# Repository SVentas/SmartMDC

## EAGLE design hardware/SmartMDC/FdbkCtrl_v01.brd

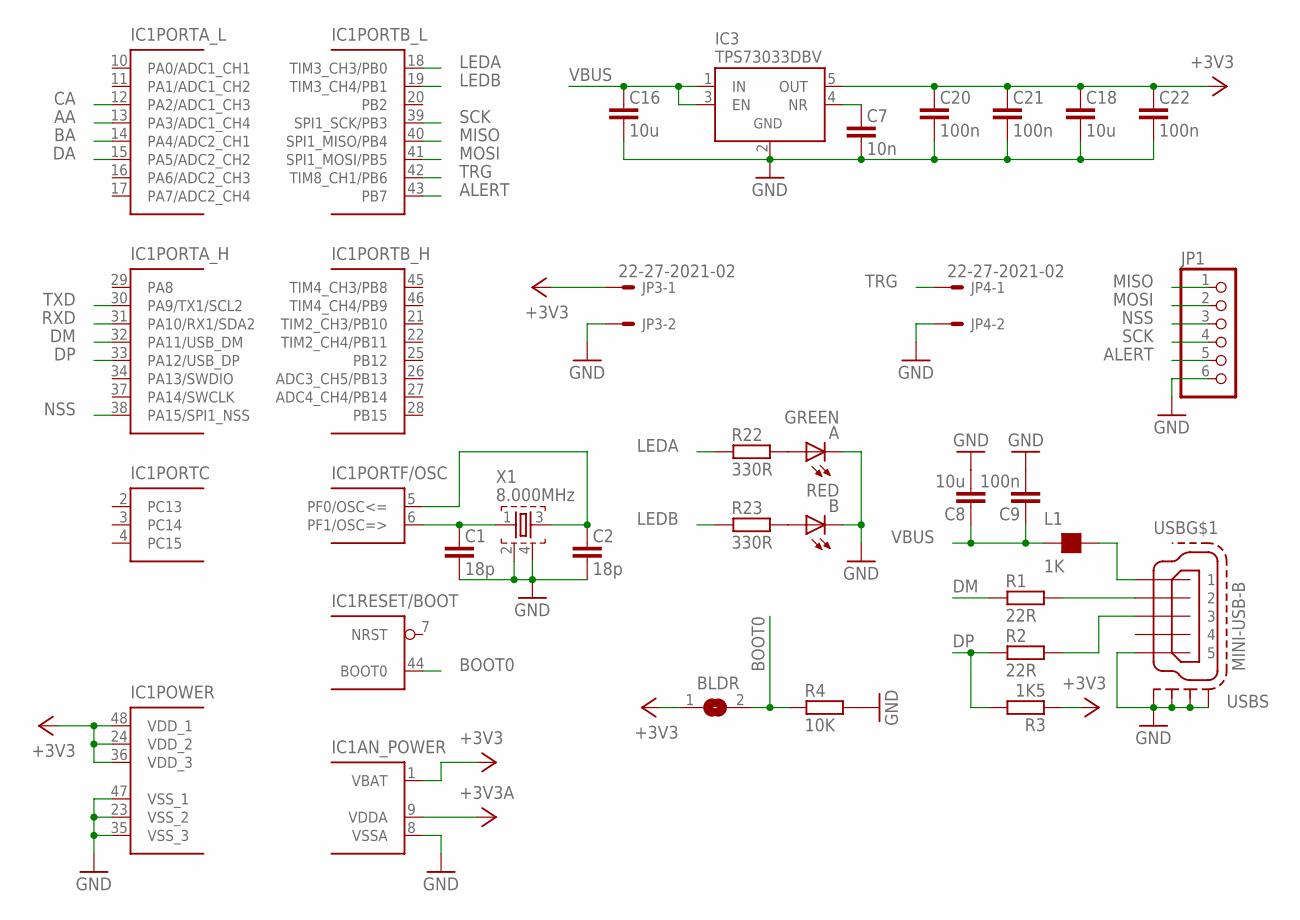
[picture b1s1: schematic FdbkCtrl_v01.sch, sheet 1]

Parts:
A: GREEN; CHIPLED_0805
B: RED; CHIPLED_0805
BLDR: SJ
C1, C2: 18p; C0603G
C7: 10n; C0402G
C8, C16, C18: 10u; C0805G
C9: 100n; C0603G
C20, C21, C22: 100n; C0402G
IC1: STM32F303CXT6; LQFP48
IC3: TPS73033DBV; SOT23-5
JP1: PINHD-1X6; 1X06
JP3, JP4: 22-27-2021-02; 6410-02
L1: 1K; L0603
R1, R2: 22R; R0603
R3: 1K5; R0603
R4: 10K; R0603G
R22, R23: 330R; R0603
USB: MINI-USB-B; 32005-201
X1: 8.000MHz; ABMM2

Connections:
+3V3: BLDR.1, C18.1, C20.1, C21.1, C22.1, IC1.1 (VBAT), IC1.24 (VDD_2), IC1.36 (VDD_3), IC1.48 (VDD_1), IC3.5 (OUT), JP3.1, R3.1
+3V3A: IC1.9 (VDDA); also elsewhere on the board
AA: IC1.13 (PA3/ADC1_CH4); also elsewhere on the board
ALERT: IC1.43 (PB7), JP1.5
BA: IC1.14 (PA4/ADC2_CH1); also elsewhere on the board
BOOT0: BLDR.2, IC1.44 (BOOT0), R4.1
CA: IC1.12 (PA2/ADC1_CH3); also elsewhere on the board
DA: IC1.15 (PA5/ADC2_CH2); also elsewhere on the board
DM: IC1.32 (PA11/USB_DM), R1.1
DP: IC1.33 (PA12/USB_DP), R2.1, R3.2
GND: A.C, B.C, C1.2, C2.2, C7.2, C8.2, C9.2, C16.2, C18.2, C20.2, C21.2, C22.2, IC1.8 (VSSA), IC1.23 (VSS_2), IC1.35 (VSS_3), IC1.47 (VSS_1), IC3.2 (GND), JP1.6, JP3.2, JP4.2, R4.2, USB.5, USB.M1 (S1), USB.M2 (S2), USB.M3 (S3), USB.M4 (S4), X1.2, X1.4; also elsewhere on the board
LEDA: IC1.18 (TIM3_CH3/PB0), R22.1
LEDB: IC1.19 (TIM3_CH4/PB1), R23.1
MISO: IC1.40 (SPI1_MISO/PB4), JP1.1
MOSI: IC1.41 (SPI1_MOSI/PB5), JP1.2
unnamed: C1.1, IC1.6 (PF1/OSC=>), X1.1
unnamed: C2.1, IC1.5 (PF0/OSC<=), X1.3
unnamed: L1.2, USB.1
unnamed: R1.2, USB.2
unnamed: R2.2, USB.3
unnamed: A.A, R22.2
unnamed: C7.1, IC3.4 (NR)
unnamed: B.A, R23.2
NSS: IC1.38 (PA15/SPI1_NSS), JP1.3
RXD: IC1.31 (PA10/RX1/SDA2)
SCK: IC1.39 (SPI1_SCK/PB3), JP1.4
TRG: IC1.42 (TIM8_CH1/PB6), JP4.1
TXD: IC1.30 (PA9/TX1/SCL2)
VBUS: C8.1, C9.1, C16.1, IC3.1 (IN), IC3.3 (EN), L1.1; also elsewhere on the board

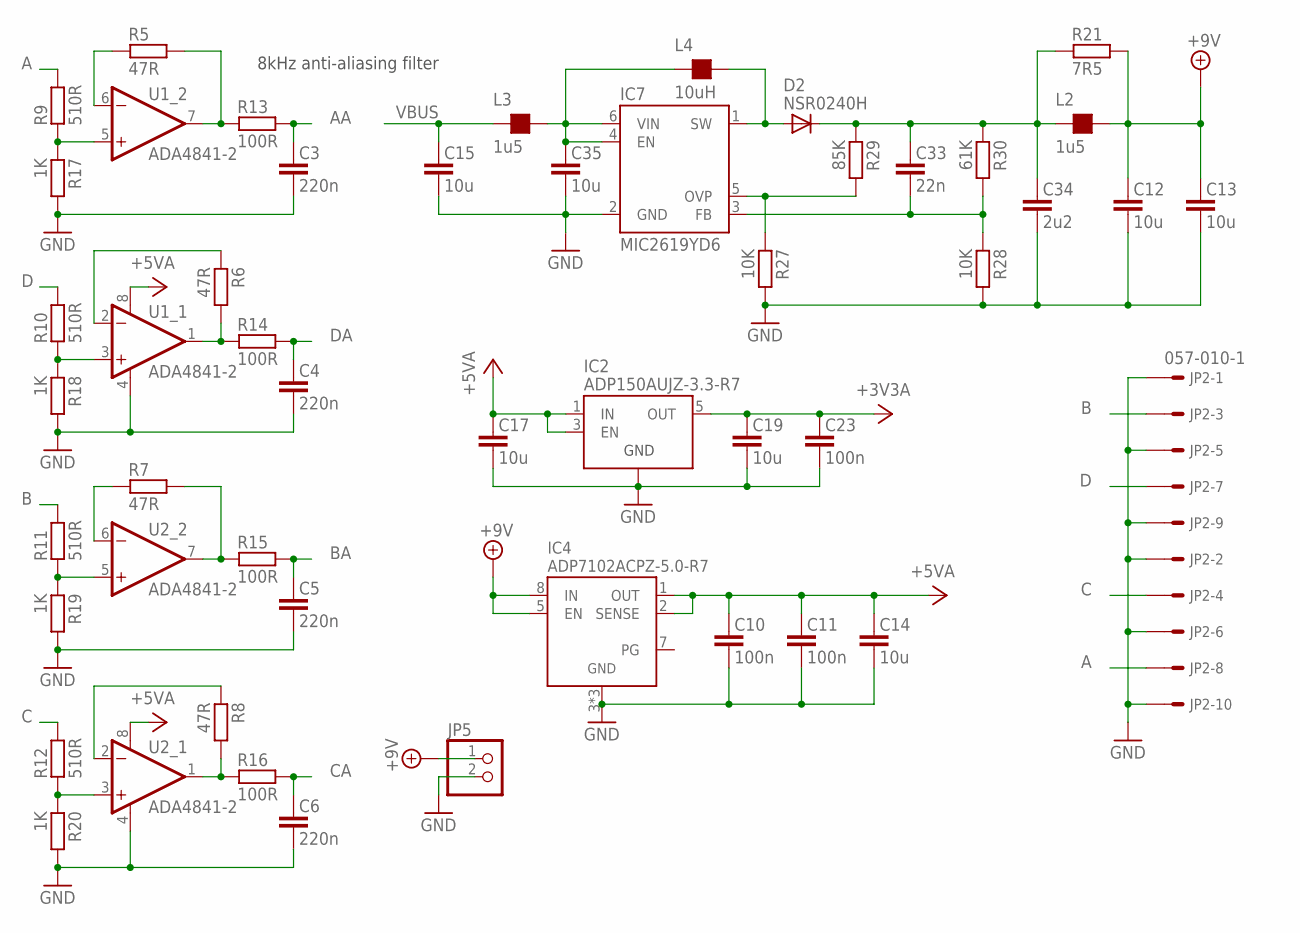
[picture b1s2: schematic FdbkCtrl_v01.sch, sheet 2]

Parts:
C3, C4, C5, C6: 220n; C0603G
C10, C11: 100n; C0603G
C12, C13, C14, C15, C17, C19, C35: 10u; C0805G
C23: 100n; C0402G
C33: 22n; C0603
C34: 2u2; C0805G
D2: NSR0240H; SOD323
IC2: ADP150AUJZ-3.3-R7; SOT23-5
IC4: ADP7102ACPZ-5.0-R7; LFCSP8
IC7: MIC2619YD6; SOT23-6
JP2: 057-010-1
JP5: PINHD-1X2; 1X02
L2, L3: 1u5; L2010
L4: 10uH; L1210
R5, R6, R7, R8: 47R; R0603
R9, R10, R11, R12: 510R; R0603
R13, R14, R15, R16: 100R; R0603
R17, R18, R19, R20: 1K; R0603G
R21: 7R5; R0805
R27, R28: 10K; R0603G
R29: 85K; R0603
R30: 61K; R0603
U1, U2: ADA4841-2; SOIC-8

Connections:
+3V3A: C19.1, C23.1, IC2.5 (OUT); also elsewhere on the board
+5VA: C10.1, C11.1, C14.1, C17.1, IC2.1 (IN), IC2.3 (EN), IC4.1 (OUT), IC4.2 (SENSE), U1.8 (V+), U2.8 (V+)
+9V: C12.1, C13.1, IC4.5 (EN), IC4.8 (IN), JP5.1, L2.2, R21.2
+9VRAW: C33.1, C34.1, D2.C, L2.1, R21.1, R29.1, R30.1
A: JP2.8, R9.2
AA: C3.1, R13.2; also elsewhere on the board
B: JP2.3, R11.2
BA: C5.1, R15.2; also elsewhere on the board
C: JP2.4, R12.2
CA: C6.1, R16.2; also elsewhere on the board
D: JP2.7, R10.2
DA: C4.1, R14.2; also elsewhere on the board
FB: C33.2, IC7.3 (FB), R28.1, R30.2
GND: C3.2, C4.2, C5.2, C6.2, C10.2, C11.2, C12.2, C13.2, C14.2, C15.2, C17.2, C19.2, C23.2, C34.2, C35.2, IC2.2 (GND), IC4.3 (GND), IC4.6 (GND), IC4.EP (GND), IC7.2 (GND), JP2.1, JP2.2, JP2.5, JP2.6, JP2.9, JP2.10, JP5.2, R17.2, R18.2, R19.2, R20.2, R27.2, R28.2, U1.4 (V-), U2.4 (V-); also elsewhere on the board
unnamed: R5.2, R13.1, U1.7 (OUT)
unnamed: R6.2, R14.1, U1.1 (OUT)
unnamed: R7.2, R15.1, U2.7 (OUT)
unnamed: R8.2, R16.1, U2.1 (OUT)
unnamed: R10.1, R18.1, U1.3 (+IN)
unnamed: R11.1, R19.1, U2.5 (+IN)
unnamed: R12.1, R20.1, U2.3 (+IN)
unnamed: R5.1, U1.6 (-IN)
unnamed: R7.1, U2.6 (-IN)
unnamed: R8.1, U2.2 (-IN)
unnamed: R6.1, U1.2 (-IN)
unnamed: R9.1, R17.1, U1.5 (+IN)
OVP: IC7.5 (OVP), R27.1, R29.2
SW: D2.A, IC7.1 (SW), L4.2
VBUS: C15.1, L3.1; also elsewhere on the board
VIN: C35.1, IC7.4 (EN), IC7.6 (VIN), L3.2, L4.1

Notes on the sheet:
8kHz anti-aliasing filter

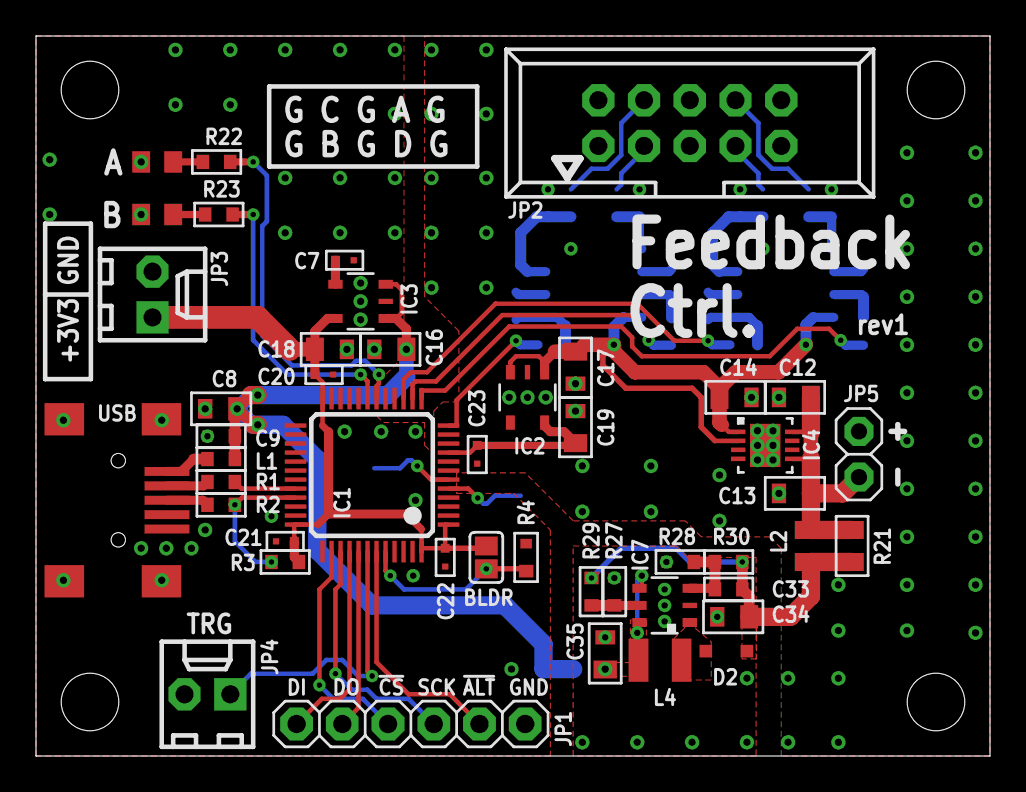
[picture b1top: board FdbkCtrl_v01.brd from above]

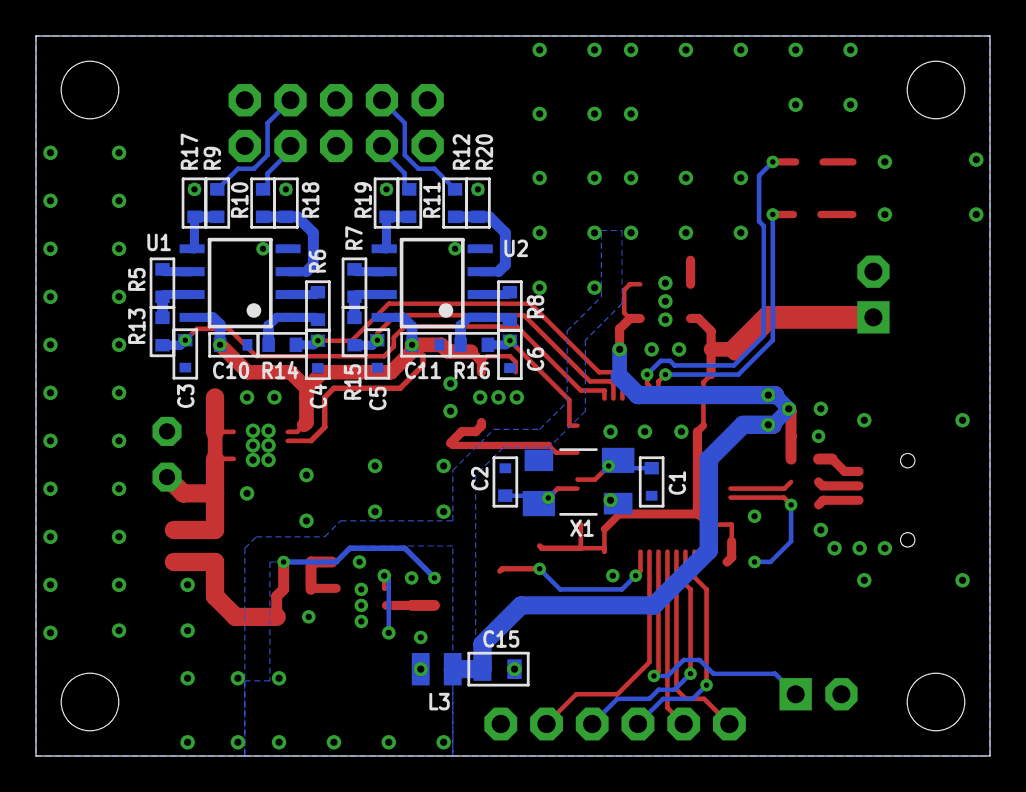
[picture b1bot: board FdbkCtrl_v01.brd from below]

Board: 2 copper layers, 53.0 x 40.0 mm, 75 parts (29 on the bottom side), 50 nets.

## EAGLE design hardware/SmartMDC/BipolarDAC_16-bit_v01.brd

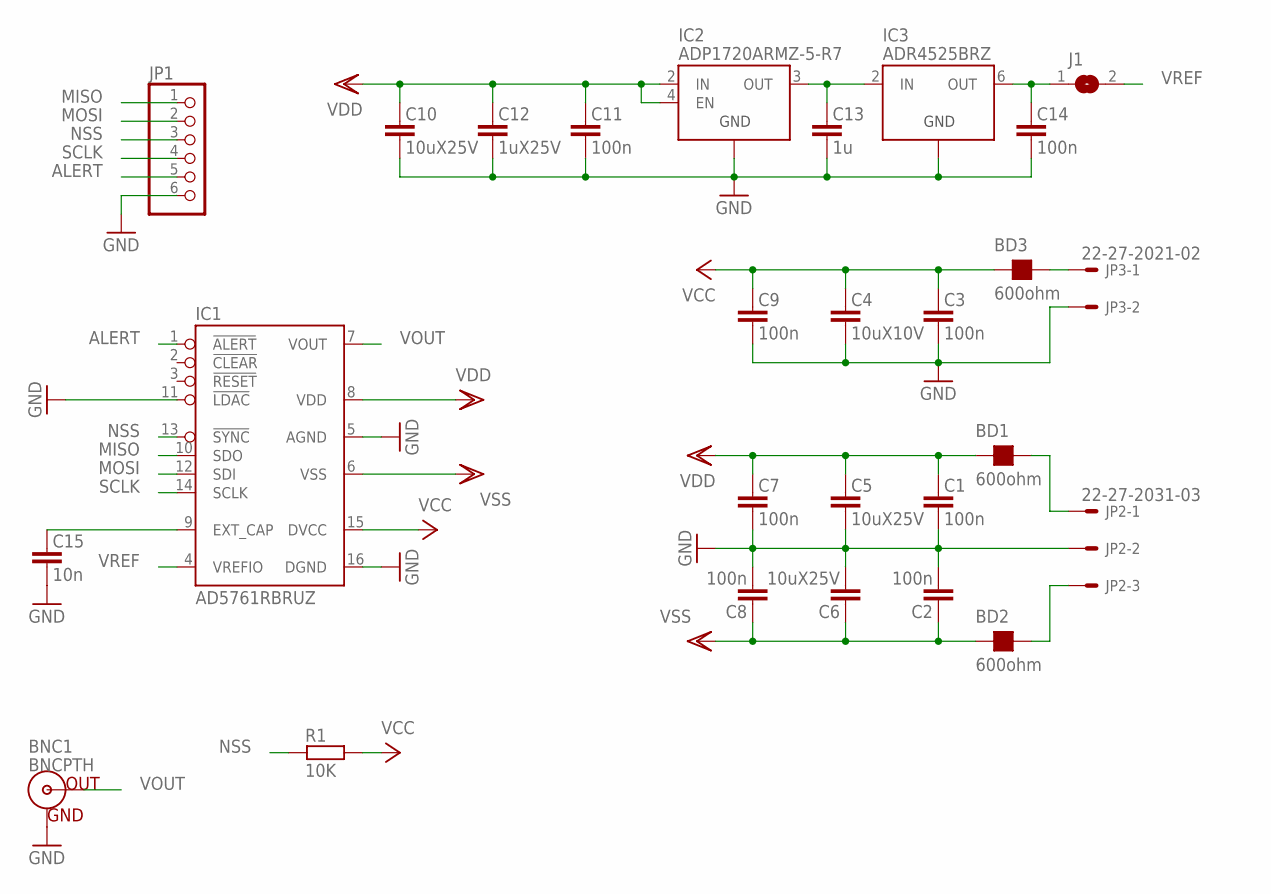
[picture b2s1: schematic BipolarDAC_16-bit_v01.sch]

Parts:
BD1, BD2, BD3: 600ohm; L0805
BNC1: BNCPTH; BNC
C1, C2, C7, C8, C11, C14: 100n; C0603G
C3, C9: 100n; C0402G
C4: 10uX10V; C0805G
C5, C6, C10: 10uX25V; C1206G
C12: 1uX25V; C0603G
C13: 1u; C0603G
C15: 10n; C0603G
IC1: AD5761RBRUZ; TSSOP16
IC2: ADP1720ARMZ-5-R7; MSOP8
IC3: ADR4525BRZ; SOIC-8
J1: SJS
JP1: PINHD-1X6; 1X06
JP2: 22-27-2031-03; 6410-03
JP3: 22-27-2021-02; 6410-02
R1: 10K; R0603G

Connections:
5VOUT: C13.1, IC2.3 (OUT), IC3.2 (IN)
ALERT: IC1.1 (!ALERT), JP1.5
GND: BNC1.GND, C1.2, C2.2, C3.2, C4.2, C5.2, C6.2, C7.2, C8.2, C9.2, C10.2, C11.2, C12.2, C13.2, C14.2, C15.2, IC1.5 (AGND), IC1.11 (!LDAC), IC1.16 (DGND), IC2.1 (GND), IC2.5 (GND), IC2.6 (GND), IC2.7 (GND), IC2.8 (GND), IC3.4 (GND), JP1.6, JP2.2, JP3.2
MISO: IC1.10 (SDO), JP1.1
MOSI: IC1.12 (SDI), JP1.2
unnamed: C15.1, IC1.9 (EXT_CAP)
NSS: IC1.13 (!SYNC), JP1.3, R1.1
SCLK: IC1.14 (SCLK), JP1.4
VCC: BD3.1, C3.1, C4.1, C9.1, IC1.15 (DVCC), R1.2
VCC_IN: BD3.2, JP3.1
VDD: BD1.1, C1.1, C5.1, C7.1, C10.1, C11.1, C12.1, IC1.8 (VDD), IC2.2 (IN), IC2.4 (EN)
VDD_IN: BD1.2, JP2.1
VOUT: BNC1.S (OUT), IC1.7 (VOUT)
VREF: IC1.4 (VREFIO), J1.2
VREF_OUT: C14.1, IC3.6 (OUT), J1.1
VSS: BD2.1, C2.1, C6.1, C8.1, IC1.6 (VSS)
VSS_IN: BD2.2, JP2.3

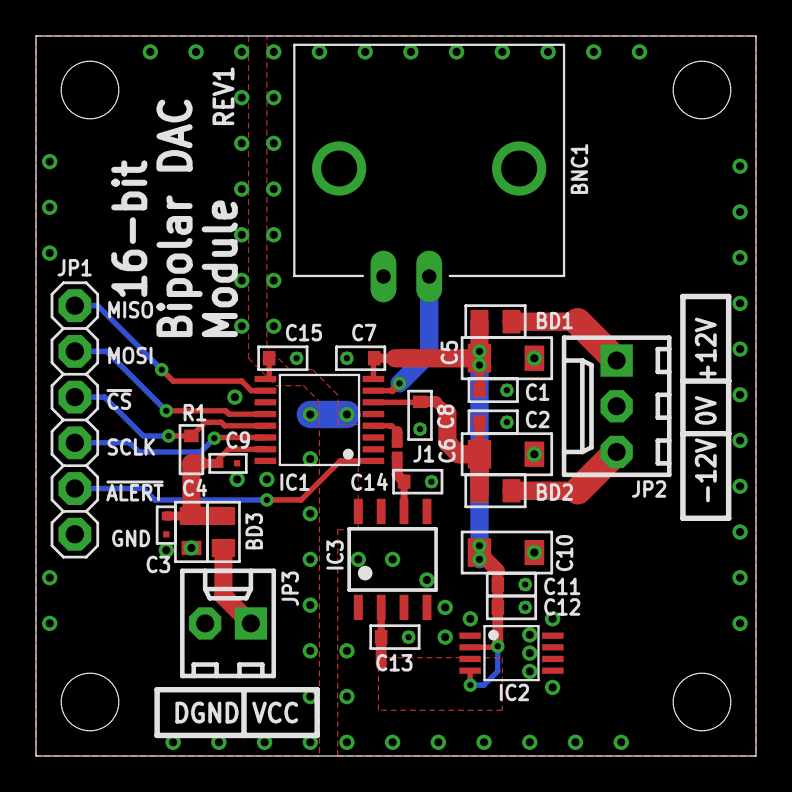
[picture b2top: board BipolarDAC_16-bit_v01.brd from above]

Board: 2 copper layers, 40.0 x 40.0 mm, 27 parts (0 on the bottom side), 17 nets.

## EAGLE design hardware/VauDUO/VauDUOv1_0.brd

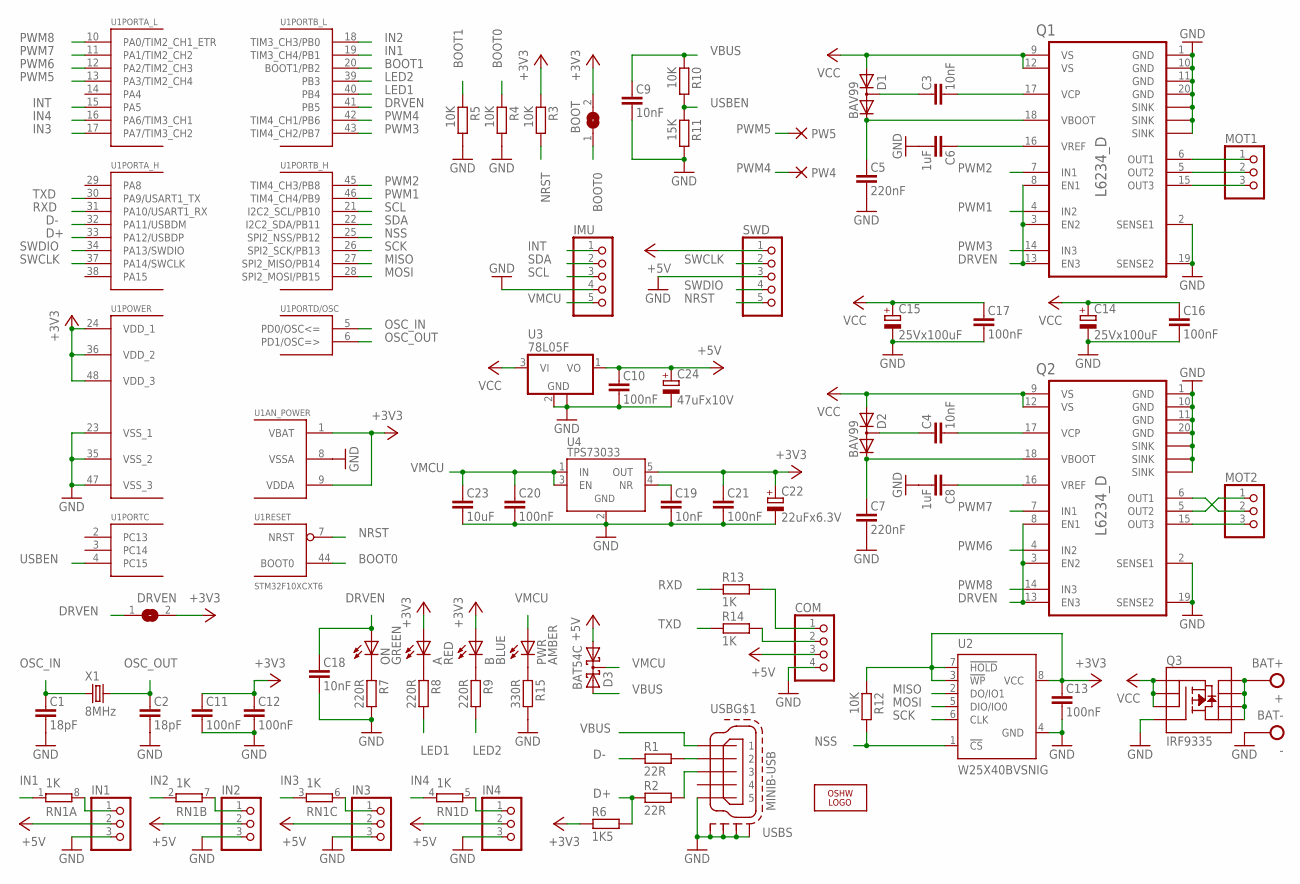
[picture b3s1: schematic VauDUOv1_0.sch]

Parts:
+: BAT+; PAD20S
-: BAT-; PAD20R
A: RED; CHIPLED_0805
B: BLUE; CHIPLED_0805
BOOT: SJ
C1, C2: 18pF; C0603G
C3, C4: 10nF; C0603
C5, C7: 220nF; C0603G
C6, C8: 1uF; C0603G
C9, C18, C19: 10nF; C0603G
C10, C11, C12, C13, C16, C17, C20, C21: 100nF; C0603G
C14, C15: 25Vx100uF; E2,5-7
C22: 22uFx6.3V; SMC_A
C23: 10uF; C0805
C24: 47uFx10V; SMC_B
COM: PINHD-1X4; 1X04
D1, D2: BAV99; SOT23
D3: BAT54C; SOT23
DRVEN: SJ
IMU: PINHD-1X5; 1X05
IN1, IN2, IN3, IN4: PINHD-1X3; 1X03
LOGO1: OSHW_LOGO_10MILX0350-NT; OSHW_10X350_NOTEXT
MOT1, MOT2: PINHD-1X3MOT; 1X03M
ON: GREEN; CHIPLED_0805
PW4, PW5: PAD-SMD09R; SMD09R
PWR: AMBER; CHIPLED_0805
Q1, Q2: L6234_D; POWERSO20
Q3: IRF9335; SOIC-8
R1, R2: 22R; R0603
R3, R10, R12: 10K; R0603
R4, R5: 10K; R0603G
R6: 1K5; R0603
R7: 220R; R0603G
R8, R9: 220R; R0603
R11: 15K; R0603G
R13, R14: 1K; R0603
R15: 330R; R0603
RN1: 1K; CAY16
SWD: PINHD-1X5; 1X05
U1: STM32F10XCXT6; LQFP48
U2: W25X40BVSNIG; SOIC-8
U3: 78L05F; SOT89
U4: TPS73033; SOT23-5
USB: MINIB-USB; 32005-201
X1: 8MHz; HC49/S

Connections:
+3V3: A.A, B.A, BOOT.2, C11.1, C12.1, C13.1, C21.1, C22.+, DRVEN.2, R3.1, R6.1, R12.1, U1.1 (VBAT), U1.9 (VDDA), U1.24 (VDD_1), U1.36 (VDD_2), U1.48 (VDD_3), U2.3 (!WP), U2.7 (!HOLD), U2.8 (VCC), U4.5 (OUT)
+5V: C10.1, C24.+, COM.3, D3.1 (A1), IN1.2, IN2.2, IN3.2, IN4.2, SWD.1, U3.1 (VO)
BOOT0: BOOT.1, R4.1, U1.44 (BOOT0)
BOOT1: R5.1, U1.20 (BOOT1/PB2)
D+: R2.1, R6.2, U1.33 (PA12/USBDP)
D-: R1.1, U1.32 (PA11/USBDM)
DRVEN: C18.1, DRVEN.1, ON.A, Q1.3 (EN2), Q1.8 (EN1), Q1.13 (EN3), Q2.3 (EN2), Q2.8 (EN1), Q2.13 (EN3), U1.41 (PB5)
GND: -.P$1, C1.2, C2.2, C5.2, C6.2, C7.2, C8.2, C9.2, C10.2, C11.2, C12.2, C13.2, C14.-, C15.-, C16.2, C17.2, C18.2, C19.2, C20.2, C21.2, C22.-, C23.2, C24.-, COM.4, IMU.4, IN1.3, IN2.3, IN3.3, IN4.3, Q1.1 (GND), Q1.2 (SENSE1), Q1.10 (GND), Q1.11 (GND), Q1.19 (SENSE2), Q1.20 (GND), Q1.SINK1 (SINK), Q1.SINK2 (SINK), Q1.SINK3 (SINK), Q2.1 (GND), Q2.2 (SENSE1), Q2.10 (GND), Q2.11 (GND), Q2.19 (SENSE2), Q2.20 (GND), Q2.SINK1 (SINK), Q2.SINK2 (SINK), Q2.SINK3 (SINK), Q3.4 (G), R4.2, R5.2, R7.2, R11.2, R15.2, SWD.3, U1.8 (VSSA), U1.23 (VSS_1), U1.35 (VSS_2), U1.47 (VSS_3), U2.4 (GND), U3.2 (GND), U3.2@1 (GND), U4.2 (GND), USB.5, USB.M1 (S1), USB.M2 (S2), USB.M3 (S3), USB.M4 (S4)
IN1: RN1.1, U1.19 (TIM3_CH4/PB1)
IN2: RN1.2 (1), U1.18 (TIM3_CH3/PB0)
IN3: RN1.3 (1), U1.17 (PA7/TIM3_CH2)
IN4: RN1.4 (1), U1.16 (PA6/TIM3_CH1)
INT: IMU.1, U1.15 (PA5)
LED1: R8.2, U1.40 (PB4)
LED2: R9.2, U1.39 (PB3)
MISO: U1.27 (SPI2_MISO/PB14), U2.2 (DO/IO1)
MOSI: U1.28 (SPI2_MOSI/PB15), U2.5 (DIO/IO0)
unnamed: R1.2, USB.2
unnamed: R2.2, USB.3
unnamed: IN1.1, RN1.8 (2)
unnamed: IN2.1, RN1.7 (2)
unnamed: IN3.1, RN1.6 (2)
unnamed: IN4.1, RN1.5 (2)
unnamed: MOT2.1, Q2.5 (OUT2)
unnamed: MOT2.2, Q2.6 (OUT1)
unnamed: C4.2, Q2.17 (VCP)
unnamed: C3.2, Q1.17 (VCP)
unnamed: MOT1.1, Q1.6 (OUT1)
unnamed: MOT1.2, Q1.5 (OUT2)
unnamed: MOT1.3, Q1.15 (OUT3)
unnamed: C6.1, Q1.16 (VREF)
unnamed: C8.1, Q2.16 (VREF)
unnamed: MOT2.3, Q2.15 (OUT3)
unnamed: C3.1, D1.3 (AC)
unnamed: C4.1, D2.3 (AC)
unnamed: C7.1, D2.2 (C), Q2.18 (VBOOT)
unnamed: C5.1, D1.2 (C), Q1.18 (VBOOT)
unnamed: ON.C, R7.1
unnamed: A.C, R8.1
unnamed: B.C, R9.1
unnamed: C19.1, U4.4 (NR)
unnamed: COM.1, R13.2
unnamed: COM.2, R14.2
unnamed: PWR.C, R15.1
NRST: R3.2, SWD.5, U1.7 (NRST)
NSS: R12.2, U1.25 (SPI2_NSS/PB12), U2.1 (!CS)
OSC_IN: C1.1, U1.5 (PD0/OSC<=), X1.1
OSC_OUT: C2.1, U1.6 (PD1/OSC=>), X1.2
PWM1: Q1.4 (IN2), U1.46 (TIM4_CH4/PB9)
PWM2: Q1.7 (IN1), U1.45 (TIM4_CH3/PB8)
PWM3: Q1.14 (IN3), U1.43 (TIM4_CH2/PB7)
PWM4: PW4.PAD, U1.42 (TIM4_CH1/PB6)
PWM5: PW5.PAD, U1.13 (PA3/TIM2_CH4)
PWM6: Q2.4 (IN2), U1.12 (PA2/TIM2_CH3)
PWM7: Q2.7 (IN1), U1.11 (PA1/TIM2_CH2)
PWM8: Q2.14 (IN3), U1.10 (PA0/TIM2_CH1_ETR)
RXD: R13.1, U1.31 (PA10/USART1_RX)
SCK: U1.26 (SPI2_SCK/PB13), U2.6 (CLK)
SCL: IMU.3, U1.21 (I2C2_SCL/PB10)
SDA: IMU.2, U1.22 (I2C2_SDA/PB11)
SWCLK: SWD.2, U1.37 (PA14/SWCLK)
SWDIO: SWD.4, U1.34 (PA13/SWDIO)
TXD: R14.1, U1.30 (PA9/USART1_TX)
USBEN: R10.2, R11.1, U1.4 (PC15)
VBAT: +.P$1, Q3.5 (D), Q3.6 (D), Q3.7 (D), Q3.8 (D)
VBUS: C9.1, D3.2 (A2), R10.1, USB.1
VCC: C14.+, C15.+, C16.1, C17.1, D1.1 (A), D2.1 (A), Q1.9 (VS), Q1.12 (VS), Q2.9 (VS), Q2.12 (VS), Q3.1 (S), Q3.2 (S), Q3.3 (S), U3.3 (VI)
VMCU: C20.1, C23.1, D3.3 (CC), IMU.5, PWR.A, U4.1 (IN), U4.3 (EN)

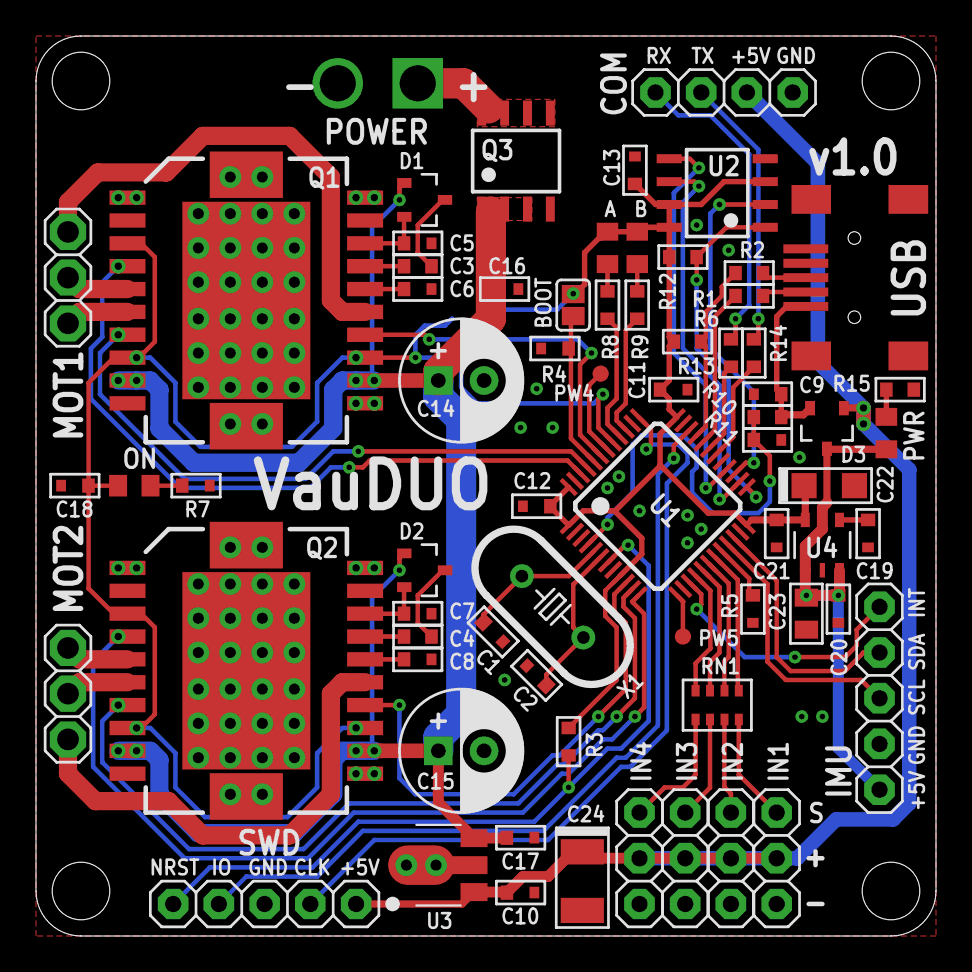
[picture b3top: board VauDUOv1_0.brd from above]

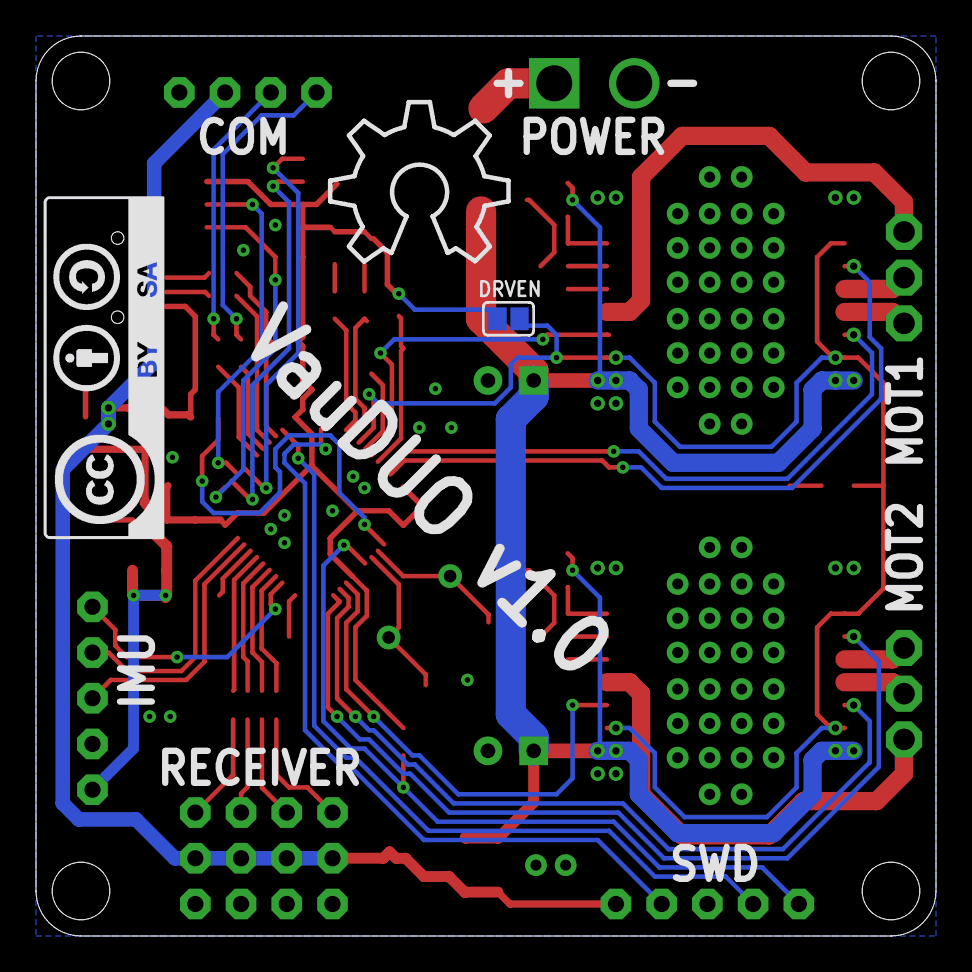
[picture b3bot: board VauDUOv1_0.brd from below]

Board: 2 copper layers, 50.0 x 50.0 mm, 72 parts (2 on the bottom side), 68 nets.

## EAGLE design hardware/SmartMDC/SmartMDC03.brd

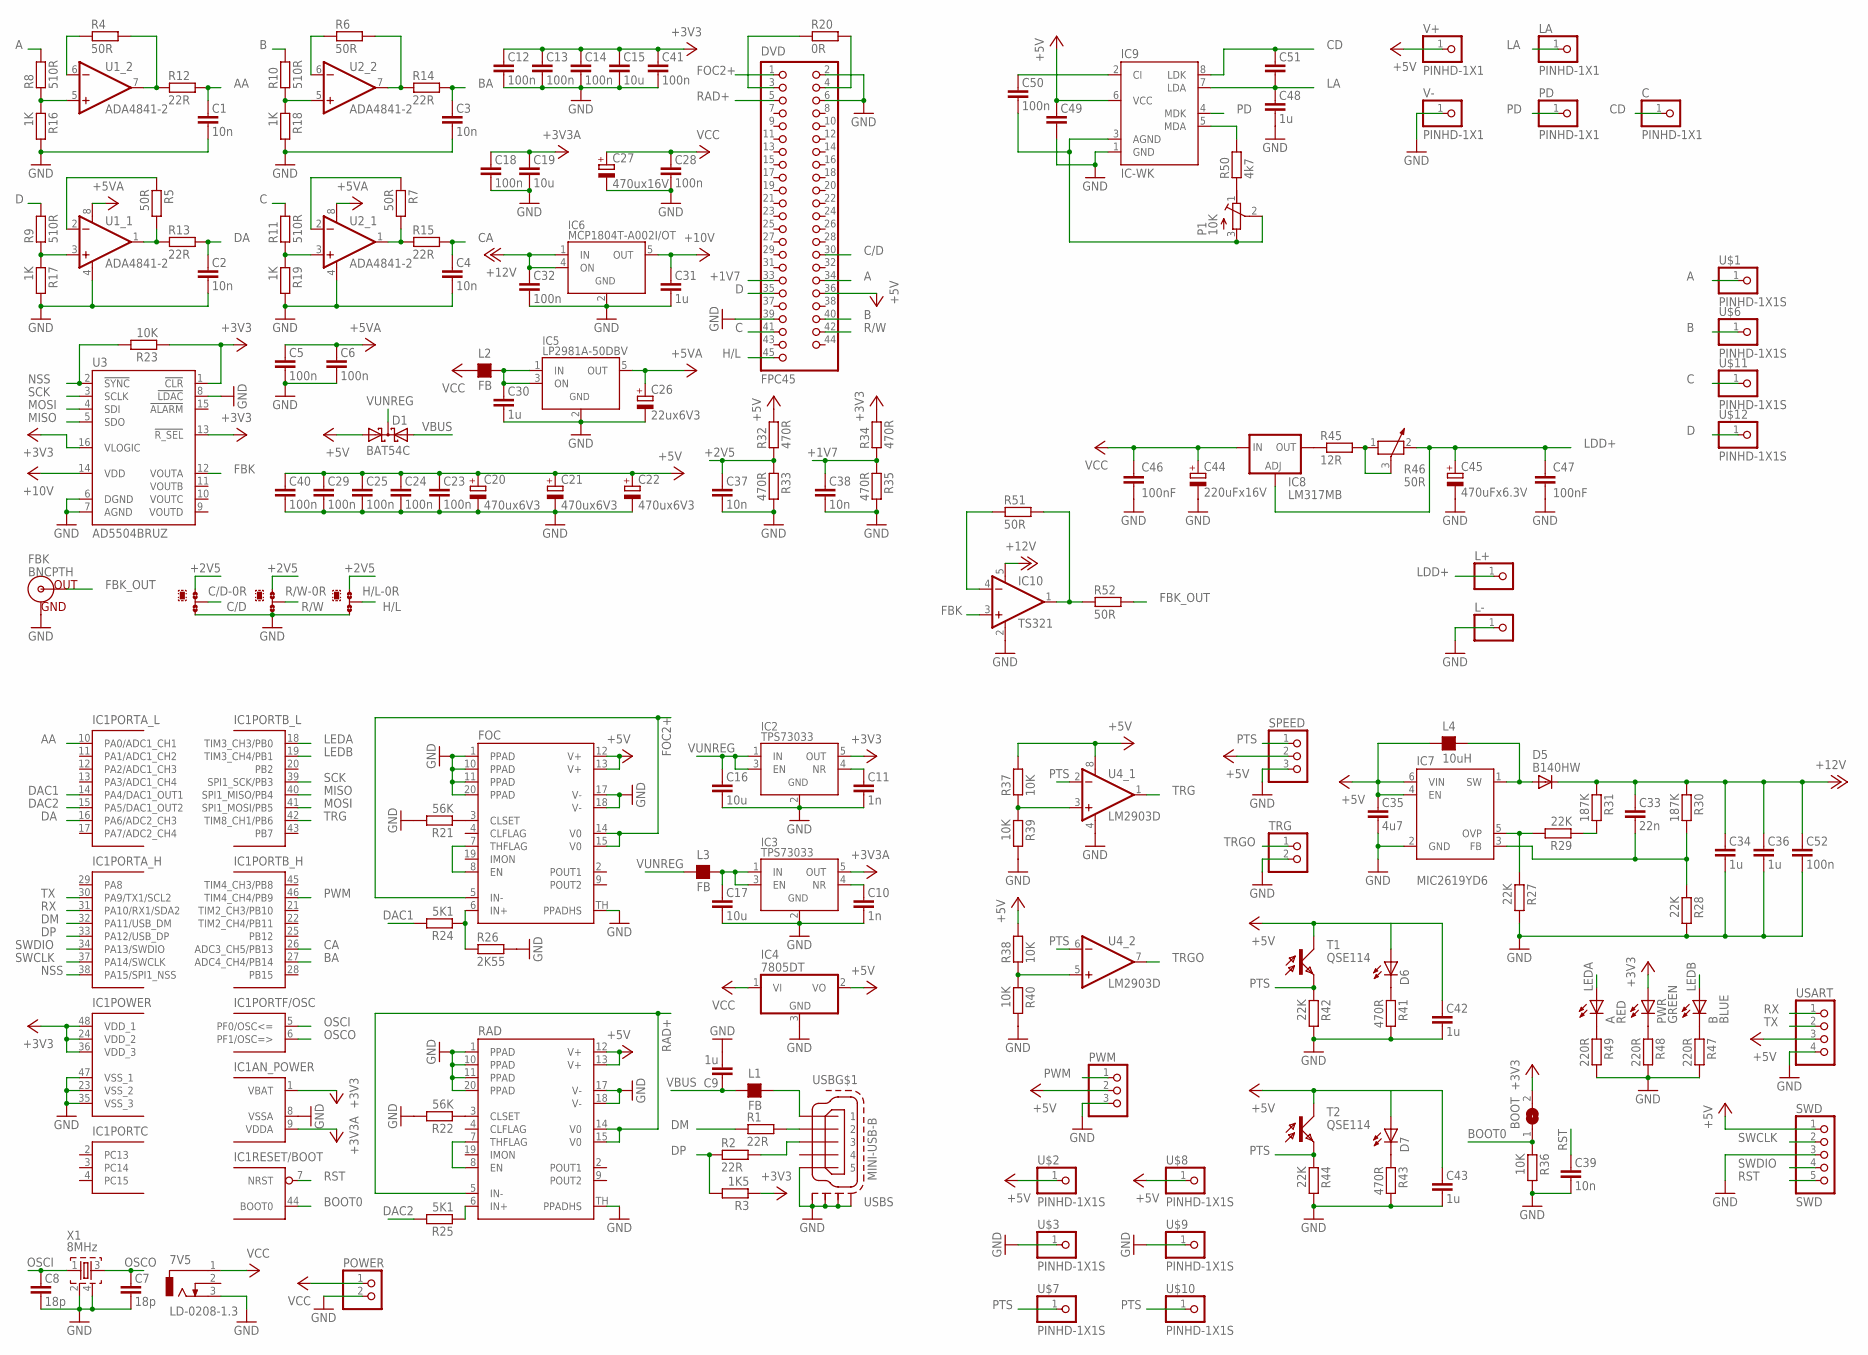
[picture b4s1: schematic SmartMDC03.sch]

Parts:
7V5: LD-0208-1.3; LD-0208
A: RED; CHIPLED_0805
B: BLUE; CHIPLED_0805
BOOT: SJ
C: PINHD-1X1; 1X01
C1, C2, C3, C4, C37, C38, C39: 10n; C0603G
C5, C6, C12, C13, C14, C18, C23, C24, C25, C28, C29, C32, C40, C41, C52: 100n; C0603G
C7, C8: 18p; C0603G
C9, C30, C31, C34, C36, C42, C43: 1u; C0603G
C10, C11: 1n; C0603G
C15, C16, C17, C19: 10u; C0805G
C20, C21, C22: 470ux6V3; SMC_D
C26: 22ux6V3; SMC_A
C27: 470ux16V; E2,5-7
C33: 22n; C0603
C35: 4u7; C0603G
C44: 220uFx16V; E3,5-8
C45: 470uFx6.3V; E3,5-8
C46, C47: 100nF; C050-024X044
C48: 1u; C0805
C49, C51: C_EU_C0805; C0805
C50: 100n; C0805
C/D: 0R-JUMPA; A0R-JMP
D1: BAT54C; SOT23
D5: B140HW; SOD123
D6, D7: OP240
DVD: FPC45
FBK: BNCPTH; BNC
FOC: OPA569; SO-20
H/L: 0R-JUMPA; A0R-JMP
IC1: STM32F303CXT6; LQFP48
IC2, IC3: TPS73033; SOT23-5
IC4: 7805DT; TO252
IC5: LP2981A-50DBV; SOT23-5
IC6: MCP1804T-A002I/OT; SOT23-5
IC7: MIC2619YD6; SOT23-6
IC8: LM317MB; TO220L1
IC9: IC-WK; SOIC-8
IC10: TS321; SOT23-5
L1, L2, L3: FB; L0603
L4: 10uH; L1210
L+: PINHD-1X1; 1X01
L-: PINHD-1X1; 1X01
LA: PINHD-1X1; 1X01
P1: 10K; RTRIM3165W
PD: PINHD-1X1; 1X01
POWER: PINHD-1X2; 1X02
PWM: PINHD-1X3; 1X03
PWR: GREEN; CHIPLED_0805
R1, R2, R12, R13, R14, R15: 22R; R0603
R3: 1K5; R0603
R4, R5, R6, R7, R51, R52: 50R; R0603
R8, R9, R10, R11: 510R; R0603
R16, R17, R18, R19: 1K; R0603G
R20: 0R; R0603
R21, R22: 56K; R0603G
R23, R37, R38: 10K; R0603
R24, R25: 5K1; R0603
R26: 2K55; R0603G
R27, R28, R42, R44: 22K; R0603G
R29: 22K; R0603
R30, R31: 187K; R0603
R32, R34: 470R; R0603
R33, R35, R41, R43: 470R; R0603G
R36, R39, R40: 10K; R0603G
R45: 12R; 0207/7
R46: 50R; PT-SPIN
R47, R48, R49: 220R; R0603G
R50: 4k7; R0805
R/W: 0R-JUMPA; A0R-JMP
RAD: OPA569; SO-20
SPEED: PINHD-1X3; 1X03
SWD: SWD; 1X05
T1, T2: QSE114
TRG: PINHD-1X2; 1X02
U1, U2: ADA4841-2; SOIC-8
U3: AD5504BRUZ; TSSOP16
U4: LM2903D; SOIC-8
U$1, U$2, U$3, U$6, U$7, U$8, U$9, U$10, U$11, U$12: PINHD-1X1S; 1X01S
USART: PINHD-1X4; 1X04
USB: MINI-USB-B; 32005-201
V+: PINHD-1X1; 1X01
V-: PINHD-1X1; 1X01
X1: 8MHz; ABMM2

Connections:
+1V7: C38.1, DVD.33, R34.1, R35.1
+2V5: C37.1, C/D.1, H/L.1, R32.1, R33.1, R/W.1
+3V3: BOOT.2, C12.1, C13.1, C14.1, C15.1, C41.1, IC1.1 (VBAT), IC1.24 (VDD_2), IC1.36 (VDD_3), IC1.48 (VDD_1), IC2.5 (OUT), PWR.A, R3.1, R23.1, R34.2, U3.1 (!CLR), U3.13 (!R_SEL), U3.16 (VLOGIC)
+3V3A: C18.1, C19.1, IC1.9 (VDDA), IC3.5 (OUT)
+5V: C20.+, C21.+, C22.+, C23.1, C24.1, C25.1, C29.1, C35.1, C40.1, C42.1, C43.1, C49.1, D1.1 (A1), D6.A, D7.A, DVD.36, FOC.12 (V+), FOC.13 (V+), IC4.2 (VO), IC7.4 (EN), IC7.6 (VIN), IC9.6 (VCC), L4.1, PWM.2, R32.2, R37.2, R38.2, RAD.12 (V+), RAD.13 (V+), SPEED.2, SWD.1, T1.C, T2.C, U4.8 (V+), U$2.1, U$8.1, USART.3, V+.1
+5VA: C5.1, C6.1, C26.+, IC5.5 (OUT), U1.8 (V+), U2.8 (V+)
+10V: C31.1, IC6.5 (OUT), U3.14 (VDD)
+12V: C32.1, C33.1, C34.1, C36.1, C52.1, D5.C, IC6.1 (IN), IC6.4 (ON), IC10.5 (V+), R30.1, R31.1
A: DVD.34, R8.2, U$1.1
AA: C1.1, IC1.10 (PA0/ADC1_CH1), R12.2
B: DVD.40, R10.2, U$6.1
BA: C3.1, IC1.27 (ADC4_CH4/PB14), R14.2
BOOT0: BOOT.1, IC1.44 (BOOT0), R36.1
C: DVD.41, R11.2, U$11.1
C/D: C/D.2, DVD.30
CA: C4.1, IC1.26 (ADC3_CH5/PB13), R15.2
CD: C.1, C51.1, IC9.8 (LDK)
D: DVD.35, R9.2, U$12.1
DA: C2.1, IC1.16 (PA6/ADC2_CH3), R13.2
DAC1: IC1.14 (PA4/DAC1_OUT1), R24.2
DAC2: IC1.15 (PA5/DAC1_OUT2), R25.2
DM: IC1.32 (PA11/USB_DM), R1.1
DP: IC1.33 (PA12/USB_DP), R2.1, R3.2
FBK: IC10.3 (+IN), U3.12 (VOUTA)
FBK_OUT: FBK.S (OUT), R52.2
FOC2+: DVD.1, FOC.5 (IN-), FOC.14 (V0), FOC.15 (V0)
GND: 7V5.3, C1.2, C2.2, C3.2, C4.2, C5.2, C6.2, C7.2, C8.2, C9.2, C10.2, C11.2, C12.2, C13.2, C14.2, C15.2, C16.2, C17.2, C18.2, C19.2, C20.-, C21.-, C22.-, C23.2, C24.2, C25.2, C26.-, C27.-, C28.2, C29.2, C30.2, C31.2, C32.2, C34.2, C35.2, C36.2, C37.2, C38.2, C39.2, C40.2, C41.2, C42.2, C43.2, C44.-, C45.-, C46.2, C47.2, C48.2, C49.2, C52.2, C/D.3, DVD.2, DVD.6, DVD.39, FBK.GND, FOC.1 (PPAD), FOC.10 (PPAD), FOC.11 (PPAD), FOC.17 (V-), FOC.18 (V-), FOC.20 (PPAD), FOC.TH (PPADHS), H/L.3, IC1.8 (VSSA), IC1.23 (VSS_2), IC1.35 (VSS_3), IC1.47 (VSS_1), IC2.2 (GND), IC3.2 (GND), IC4.3 (GND), IC5.2 (GND), IC6.2 (GND), IC7.2 (GND), IC9.1 (GND), IC10.2 (V-), L-.1, POWER.2, PWM.3, R16.2, R17.2, R18.2, R19.2, R21.2, R22.2, R26.2, R27.2, R28.2, R33.2, R35.2, R36.2, R39.2, R40.2, R41.2, R42.2, R43.2, R44.2, R47.2, R48.2, R49.2, R/W.3, RAD.1 (PPAD), RAD.10 (PPAD), RAD.11 (PPAD), RAD.17 (V-), RAD.18 (V-), RAD.20 (PPAD), RAD.TH (PPADHS), SPEED.3, SWD.3, TRG.2, U1.4 (V-), U2.4 (V-), U3.6 (DGND), U3.7 (AGND), U3.8 (!LDAC), U4.4 (V-), U$3.1, U$9.1, USART.4, USB.5, USB.M1 (S1), USB.M2 (S2), USB.M3 (S3), USB.M4 (S4), V-.1, X1.2, X1.4
H/L: DVD.45, H/L.2
LA: C48.1, C51.2, IC9.7 (LDA), LA.1
LDD+: C45.+, C47.1, IC8.1 (ADJ), L+.1, R46.2
LEDA: A.A, IC1.18 (TIM3_CH3/PB0)
LEDB: B.A, IC1.19 (TIM3_CH4/PB1)
MISO: IC1.40 (SPI1_MISO/PB4), U3.5 (SDO)
MOSI: IC1.41 (SPI1_MOSI/PB5), U3.4 (SDI)
unnamed: C11.1, IC2.4 (NR)
unnamed: R9.1, R17.1, U1.3 (+IN)
unnamed: R11.1, R19.1, U2.3 (+IN)
unnamed: R10.1, R18.1, U2.5 (+IN)
unnamed: R4.2, R12.1, U1.7 (OUT)
unnamed: R5.2, R13.1, U1.1 (OUT)
unnamed: R6.2, R14.1, U2.7 (OUT)
unnamed: R7.2, R15.1, U2.1 (OUT)
unnamed: D7.C, R43.1
unnamed: R25.1, RAD.6 (IN+)
unnamed: FOC.6 (IN+), R24.1, R26.1
unnamed: C10.1, IC3.4 (NR)
unnamed: R4.1, U1.6 (-IN)
unnamed: R6.1, U2.6 (-IN)
unnamed: R7.1, U2.2 (-IN)
unnamed: R5.1, U1.2 (-IN)
unnamed: R8.1, R16.1, U1.5 (+IN)
unnamed: D6.C, R41.1
unnamed: C30.1, IC5.1 (IN), IC5.3 (ON), L2.2
unnamed: R1.2, USB.2
unnamed: R2.2, USB.3
unnamed: C17.1, IC3.1 (IN), IC3.3 (EN), L3.2
unnamed: DVD.4, R20.2
unnamed: DVD.3, R20.1
unnamed: L1.2, USB.1
unnamed: IC8.2 (OUT), R45.1
unnamed: R45.2, R46.1, R46.3
unnamed: R37.1, R39.1, U4.3 (+IN)
unnamed: B.C, R47.1
unnamed: FOC.3 (CLSET), R21.1
unnamed: R22.1, RAD.3 (CLSET)
unnamed: R38.1, R40.1, U4.5 (+IN)
unnamed: FOC.7 (THFLAG), FOC.8 (EN)
unnamed: R29.1, R31.2
unnamed: RAD.7 (THFLAG), RAD.8 (EN)
unnamed: IC7.5 (OVP), R27.1, R29.2
unnamed: C33.2, IC7.3 (FB), R28.1, R30.2
unnamed: PWR.C, R48.1
unnamed: A.C, R49.1
unnamed: P1.1 (A), R50.1
unnamed: IC10.4 (-IN), R51.1
unnamed: C50.1, IC9.2 (CI)
unnamed: IC10.1 (OUT), R51.2, R52.1
unnamed: IC9.5 (MDA), R50.2
unnamed: C50.2, IC9.3 (AGND), P1.2 (S), P1.3 (E)
NSS: IC1.38 (PA15/SPI1_NSS), R23.2, U3.2 (!SYNC)
OSCI: C8.1, IC1.5 (PF0/OSC<=), X1.1
OSCO: C7.1, IC1.6 (PF1/OSC=>), X1.3
PD: IC9.4 (MDK), PD.1
PTS: R42.1, R44.1, SPEED.1, T1.E, T2.E, U4.2 (-IN), U4.6 (-IN), U$7.1, U$10.1
PWM: IC1.46 (TIM4_CH4/PB9), PWM.1
R/W: DVD.42, R/W.2
RAD+: DVD.5, RAD.5 (IN-), RAD.14 (V0), RAD.15 (V0)
RST: C39.1, IC1.7 (NRST), SWD.5
RX: IC1.31 (PA10/RX1/SDA2), USART.1
SCK: IC1.39 (SPI1_SCK/PB3), U3.3 (SCLK)
SW: D5.A, IC7.1 (SW), L4.2
SWCLK: IC1.37 (PA14/SWCLK), SWD.2
SWDIO: IC1.34 (PA13/SWDIO), SWD.4
TRG: IC1.42 (TIM8_CH1/PB6), U4.1 (OUT)
TRGO: TRG.1, U4.7 (OUT)
TX: IC1.30 (PA9/TX1/SCL2), USART.2
VBUS: C9.1, D1.2 (A2), L1.1
VCC: 7V5.1, C27.+, C28.1, C44.+, C46.1, IC4.1 (VI), IC8.3 (IN), L2.1, POWER.1
VUNREG: C16.1, D1.3 (CC), IC2.1 (IN), IC2.3 (EN), L3.1

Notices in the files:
chibios_3.0.x/hal/boards/FDBKCTRL_REV1/board.h:
SmartMDC - Copyright (C) 2013-2016 Sarunas Vaitekonis
parts and their libraries:
dpads: Copyright (C) 2004, Bob Starr (bobstarr@mindspring.com)
